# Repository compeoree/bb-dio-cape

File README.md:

bb-dio-cape
===========

Beaglebone Digital I/O Opto Cape

This project contains the Eagle CAD (Version 6.5) files for a four layer circuit board. It maps 15 pins to digital inputs and 16 pins to digital outputs, all of which are optically isolated. It provides pads for a linear (7805) or switching (Murata OKI-78SR-5/1.5-W36H-C) 5v regulator to power the Beaglebone.

Known Issues
============

1) This cape was initially targeted to the Beaglebone White. I attempted to make it compatible with the BeagleBone Black, but I used the wrong pinmux for the eMMC pins.  
Solution:
a) Lose a few inputs/outputs when installed on a BeagleBone Black
b) Remap the affected pins

2) The TLP281 is EOL (End of Life), replace with TLP290

3) The TI DAC7678 requires a 5 volt supply in order to reach the full 5 volt output. This board only provides 3.3v, so the chip can be directly connected to the Beaglebone I2C pins. This limits the DAC to around 3 volts maximum output. A buffer, such as TI PCA9306, would need to be added to raise the DAC7678 to 5v.

4) The MAX3079E will only work in full duplex 4-wire mode. The TX/RX enables are hard wired to always on. They will not work in 2 wire mode, in the current layout.

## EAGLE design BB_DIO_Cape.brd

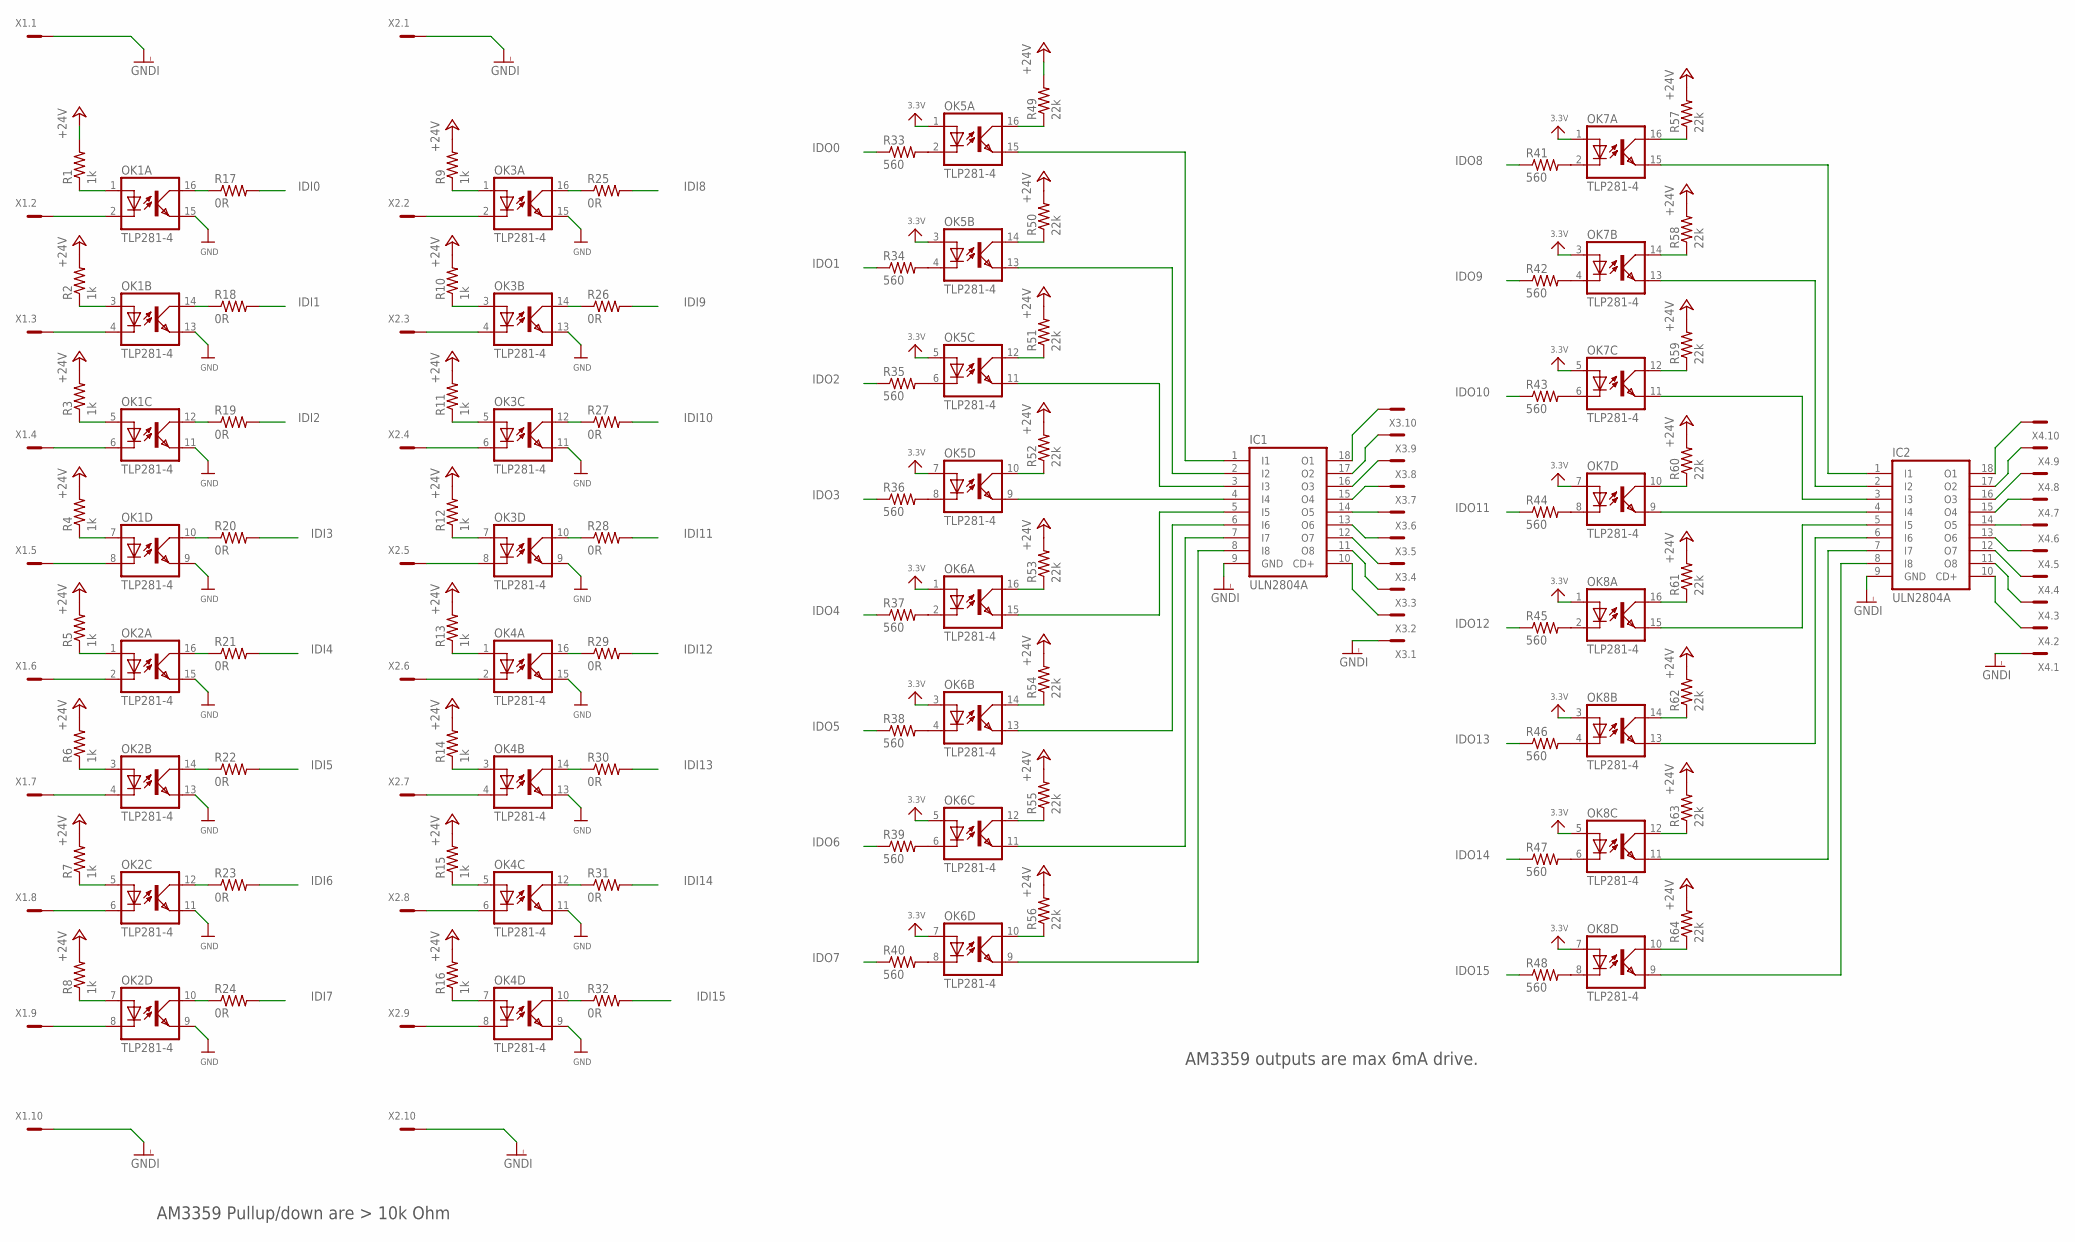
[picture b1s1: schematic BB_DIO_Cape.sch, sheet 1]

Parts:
IC1, IC2: ULN2804A; SO18W
OK1, OK2, OK3, OK4, OK5, OK6, OK7, OK8: TLP281-4; MINI-FLAT-16
R1, R2, R3, R4, R5, R6, R7, R8, R9, R10, R11, R12, R13, R14, R15, R16: 1k; R0603
R17, R18, R19, R20, R21, R22, R23, R24, R25, R26, R27, R28, R29, R30, R31, R32: 0R; R0603
R33, R34, R35, R36, R37, R38, R39, R40, R41, R42, R43, R44, R45, R46, R47, R48: 560; R0603
R49, R50, R51, R52, R53, R54, R55, R56, R57, R58, R59, R60, R61, R62, R63, R64: 22k; R0603
X1, X2, X3, X4: MC10

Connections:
3.3V: OK5.1 (A), OK5.3 (A), OK5.5 (A), OK5.7 (A), OK6.1 (A), OK6.3 (A), OK6.5 (A), OK6.7 (A), OK7.1 (A), OK7.3 (A), OK7.5 (A), OK7.7 (A), OK8.1 (A), OK8.3 (A), OK8.5 (A), OK8.7 (A); also elsewhere on the board
+24V: R1.2, R2.2, R3.2, R4.2, R5.2, R6.2, R7.2, R8.2, R9.2, R10.2, R11.2, R12.2, R13.2, R14.2, R15.2, R16.2, R49.2, R50.2, R51.2, R52.2, R53.2, R54.2, R55.2, R56.2, R57.2, R58.2, R59.2, R60.2, R61.2, R62.2, R63.2, R64.2; also elsewhere on the board
GND: OK1.9 (EMIT), OK1.11 (EMIT), OK1.13 (EMIT), OK1.15 (EMIT), OK2.9 (EMIT), OK2.11 (EMIT), OK2.13 (EMIT), OK2.15 (EMIT), OK3.9 (EMIT), OK3.11 (EMIT), OK3.13 (EMIT), OK3.15 (EMIT), OK4.9 (EMIT), OK4.11 (EMIT), OK4.13 (EMIT), OK4.15 (EMIT); also elsewhere on the board
GNDI: IC1.9 (GND), IC2.9 (GND), X1.1, X1.10, X2.1, X2.10, X3.1, X4.1; also elsewhere on the board
IDI0: R17.2; also elsewhere on the board
IDI1: R18.2; also elsewhere on the board
IDI2: R19.2; also elsewhere on the board
IDI3: R20.2; also elsewhere on the board
IDI4: R21.2; also elsewhere on the board
IDI5: R22.2; also elsewhere on the board
IDI6: R23.2; also elsewhere on the board
IDI7: R24.2; also elsewhere on the board
IDI8: R25.2; also elsewhere on the board
IDI9: R26.2; also elsewhere on the board
IDI10: R27.2; also elsewhere on the board
IDI11: R28.2; also elsewhere on the board
IDI12: R29.2; also elsewhere on the board
IDI13: R30.2; also elsewhere on the board
IDI14: R31.2; also elsewhere on the board
IDI15: R32.2
IDO0: R33.1; also elsewhere on the board
IDO1: R34.1; also elsewhere on the board
IDO2: R35.1; also elsewhere on the board
IDO3: R36.1; also elsewhere on the board
IDO4: R37.1; also elsewhere on the board
IDO5: R38.1; also elsewhere on the board
IDO6: R39.1; also elsewhere on the board
IDO7: R40.1; also elsewhere on the board
IDO8: R41.1; also elsewhere on the board
IDO9: R42.1; also elsewhere on the board
IDO10: R43.1; also elsewhere on the board
IDO11: R44.1; also elsewhere on the board
IDO12: R45.1; also elsewhere on the board
IDO13: R46.1; also elsewhere on the board
IDO14: R47.1; also elsewhere on the board
IDO15: R48.1; also elsewhere on the board
unnamed: OK4.8 (C), X2.9
unnamed: OK4.7 (A), R16.1
unnamed: OK4.5 (A), R15.1
unnamed: OK4.6 (C), X2.8
unnamed: OK4.4 (C), X2.7
unnamed: OK4.3 (A), R14.1
unnamed: OK4.2 (C), X2.6
unnamed: OK4.1 (A), R13.1
unnamed: OK3.8 (C), X2.5
unnamed: OK3.7 (A), R12.1
unnamed: OK3.6 (C), X2.4
unnamed: OK3.5 (A), R11.1
unnamed: OK3.4 (C), X2.3
unnamed: OK3.3 (A), R10.1
unnamed: OK4.10 (COL), R32.1
unnamed: OK4.12 (COL), R31.1
unnamed: OK4.14 (COL), R30.1
unnamed: OK4.16 (COL), R29.1
unnamed: OK3.10 (COL), R28.1
unnamed: OK3.12 (COL), R27.1
unnamed: OK3.14 (COL), R26.1
unnamed: OK2.10 (COL), R24.1
unnamed: OK2.12 (COL), R23.1
unnamed: OK2.14 (COL), R22.1
unnamed: OK2.16 (COL), R21.1
unnamed: OK1.10 (COL), R20.1
unnamed: OK1.12 (COL), R19.1
unnamed: OK1.14 (COL), R18.1
unnamed: OK1.4 (C), X1.3
unnamed: OK1.3 (A), R2.1
unnamed: OK1.5 (A), R3.1
unnamed: OK1.6 (C), X1.4
unnamed: OK1.7 (A), R4.1
unnamed: OK1.8 (C), X1.5
unnamed: OK2.2 (C), X1.6
unnamed: OK2.1 (A), R5.1
unnamed: OK2.3 (A), R6.1
unnamed: OK2.4 (C), X1.7
unnamed: OK2.5 (A), R7.1
unnamed: OK2.6 (C), X1.8
unnamed: OK2.7 (A), R8.1
unnamed: OK2.8 (C), X1.9
unnamed: OK1.2 (C), X1.2
unnamed: OK1.1 (A), R1.1
unnamed: OK1.16 (COL), R17.1
unnamed: OK3.2 (C), X2.2
unnamed: OK3.1 (A), R9.1
unnamed: OK3.16 (COL), R25.1
unnamed: OK5.2 (C), R33.2
unnamed: OK5.4 (C), R34.2
unnamed: OK5.6 (C), R35.2
unnamed: OK5.8 (C), R36.2
unnamed: OK6.2 (C), R37.2
unnamed: OK6.4 (C), R38.2
unnamed: OK6.6 (C), R39.2
unnamed: OK6.8 (C), R40.2
unnamed: OK7.2 (C), R41.2
unnamed: OK7.4 (C), R42.2
unnamed: OK7.6 (C), R43.2
unnamed: OK7.8 (C), R44.2
unnamed: OK8.2 (C), R45.2
unnamed: OK8.4 (C), R46.2
unnamed: OK8.6 (C), R47.2
unnamed: OK8.8 (C), R48.2
unnamed: OK5.16 (COL), R49.1
unnamed: OK5.14 (COL), R50.1
unnamed: OK5.12 (COL), R51.1
unnamed: OK5.10 (COL), R52.1
unnamed: OK6.16 (COL), R53.1
unnamed: OK6.14 (COL), R54.1
unnamed: OK6.12 (COL), R55.1
unnamed: OK6.10 (COL), R56.1
unnamed: IC1.8 (I8), OK6.9 (EMIT)
unnamed: IC1.7 (I7), OK6.11 (EMIT)
unnamed: IC1.6 (I6), OK6.13 (EMIT)
unnamed: IC1.5 (I5), OK6.15 (EMIT)
unnamed: IC1.4 (I4), OK5.9 (EMIT)
unnamed: IC1.3 (I3), OK5.11 (EMIT)
unnamed: IC1.2 (I2), OK5.13 (EMIT)
unnamed: IC1.1 (I1), OK5.15 (EMIT)
unnamed: OK8.14 (COL), R62.1
unnamed: OK8.12 (COL), R63.1
unnamed: OK8.10 (COL), R64.1
unnamed: IC2.8 (I8), OK8.9 (EMIT)
unnamed: IC2.7 (I7), OK8.11 (EMIT)
unnamed: IC2.6 (I6), OK8.13 (EMIT)
unnamed: IC2.5 (I5), OK8.15 (EMIT)
unnamed: OK8.16 (COL), R61.1
unnamed: OK7.10 (COL), R60.1
unnamed: OK7.12 (COL), R59.1
unnamed: IC2.4 (I4), OK7.9 (EMIT)
unnamed: IC2.3 (I3), OK7.11 (EMIT)
unnamed: IC2.2 (I2), OK7.13 (EMIT)
unnamed: OK7.14 (COL), R58.1
unnamed: OK7.16 (COL), R57.1
unnamed: IC2.1 (I1), OK7.15 (EMIT)
unnamed: IC2.18 (O1), X4.10
unnamed: IC2.10 (CD+), X4.2
unnamed: IC2.11 (O8), X4.3
unnamed: IC2.17 (O2), X4.9
unnamed: IC2.12 (O7), X4.4
unnamed: IC2.13 (O6), X4.5
unnamed: IC2.14 (O5), X4.6
unnamed: IC2.15 (O4), X4.7
unnamed: IC2.16 (O3), X4.8
unnamed: IC1.14 (O5), X3.6
unnamed: IC1.13 (O6), X3.5
unnamed: IC1.12 (O7), X3.4
unnamed: IC1.15 (O4), X3.7
unnamed: IC1.16 (O3), X3.8
unnamed: IC1.17 (O2), X3.9
unnamed: IC1.11 (O8), X3.3
unnamed: IC1.10 (CD+), X3.2
unnamed: IC1.18 (O1), X3.10

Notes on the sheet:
AM3359 Pullup/down are > 10k Ohm
AM3359 outputs are max 6mA drive.

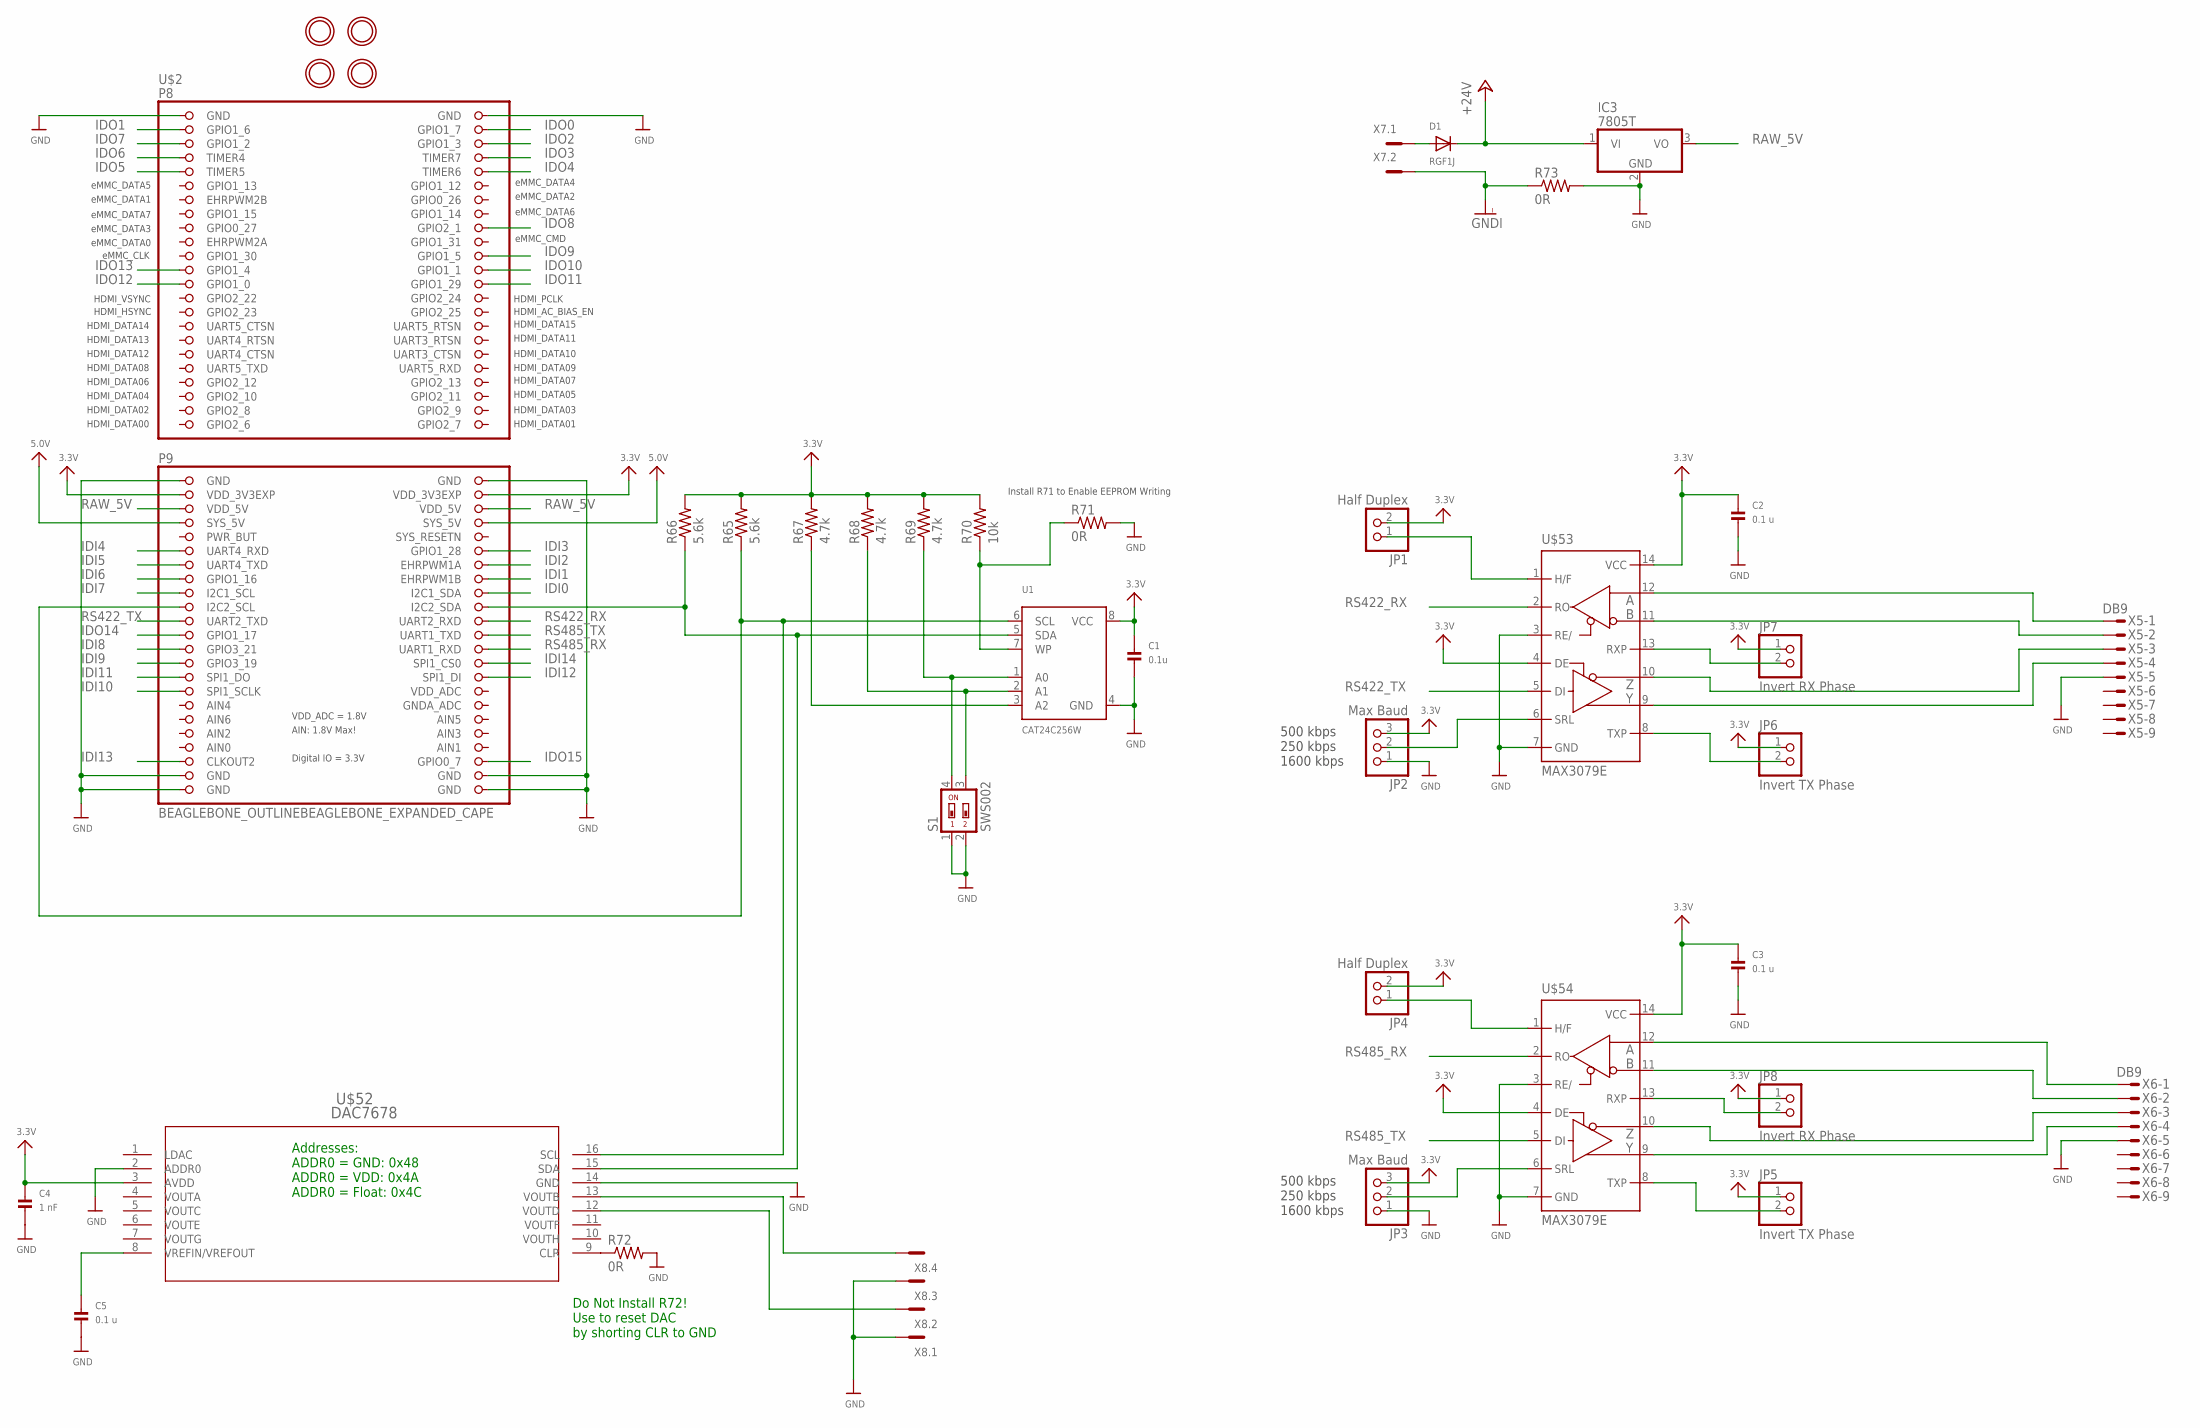
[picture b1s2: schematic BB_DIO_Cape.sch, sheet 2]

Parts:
C1: 0.1u; _0603
C2, C3, C5: 0.1 u; 0603
C4: 1 nF; 0603
D1: RGF1J; SMADIODE
IC3: 7805T; TO220H
JP1, JP4: Half Duplex; 1X02_ROUND
JP2, JP3: Max Baud; 1X03_ROUND
JP5, JP6: Invert TX Phase; 1X02_ROUND
JP7, JP8: Invert RX Phase; 1X02_ROUND
R65, R66: 5.6k; R0603
R67, R68, R69: 4.7k; R0603
R70: 10k; R0603
R71, R72: 0R; R0603
R73: 0R; M1206
S1: SWS002; SMS-002
U1: CAT24C256W; SOIC8_150MIL
U$2: BEAGLEBONE_OUTLINEBEAGLEBONE_EXPANDED_CAPE; BEAGLEBONE_SHIELD
U$22, U$23, U$71, U$72: MOUNTINGHOLE3.0THIN; MOUNTINGHOLE_3.0_PLATEDTHIN
U$52: DAC7678; PW16
U$53, U$54: MAX3079E; SO14
X5, X6: DB9; 182-009-MALE
X7: MC2
X8: MC4

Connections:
3.3V: C1.1, C2.1, C3.1, C4.1, JP1.2, JP2.3, JP3.3, JP4.2, JP5.1, JP6.1, JP7.1, JP8.1, R65.2, R66.2, R67.2, R68.2, R69.2, R70.2, U1.8 (VCC), U$2.49 (VDD_3V3EXP), U$2.50 (VDD_3V3EXP), U$52.3 (AVDD), U$53.4 (DE), U$53.14 (VCC), U$54.4 (DE), U$54.14 (VCC); also elsewhere on the board
5.0V: U$2.53 (SYS_5V), U$2.54 (SYS_5V)
+24V: D1.C, IC3.1 (VI); also elsewhere on the board
GND: C1.2, C2.2, C3.2, C4.2, C5.2, IC3.2 (GND), JP2.1, JP3.1, R71.2, R72.2, R73.2, S1.1, S1.2, U1.4 (GND), U$2.1 (GND), U$2.2 (GND), U$2.47 (GND), U$2.48 (GND), U$2.89 (GND), U$2.90 (GND), U$2.91 (GND), U$2.92 (GND), U$52.2 (ADDR0), U$52.14 (GND), U$53.3 (RE/), U$53.7 (GND), U$54.3 (RE/), U$54.7 (GND), X5.5, X6.5, X8.1, X8.3; also elsewhere on the board
GNDA_ADC: U$2.80 (GNDA_ADC)
GNDI: R73.1, X7.2; also elsewhere on the board
IDI0: U$2.64 (I2C1_SDA); also elsewhere on the board
IDI1: U$2.62 (EHRPWM1B); also elsewhere on the board
IDI2: U$2.60 (EHRPWM1A); also elsewhere on the board
IDI3: U$2.58 (GPIO1_28); also elsewhere on the board
IDI4: U$2.57 (UART4_RXD); also elsewhere on the board
IDI5: U$2.59 (UART4_TXD); also elsewhere on the board
IDI6: U$2.61 (GPIO1_16); also elsewhere on the board
IDI7: U$2.63 (I2C1_SCL); also elsewhere on the board
IDI8: U$2.71 (GPIO3_21); also elsewhere on the board
IDI9: U$2.73 (GPIO3_19); also elsewhere on the board
IDI10: U$2.77 (SPI1_SCLK); also elsewhere on the board
IDI11: U$2.75 (SPI1_DO); also elsewhere on the board
IDI12: U$2.76 (SPI1_DI); also elsewhere on the board
IDI13: U$2.87 (CLKOUT2); also elsewhere on the board
IDI14: U$2.74 (SPI1_CS0); also elsewhere on the board
IDO0: U$2.4 (GPIO1_7); also elsewhere on the board
IDO1: U$2.3 (GPIO1_6); also elsewhere on the board
IDO2: U$2.6 (GPIO1_3); also elsewhere on the board
IDO3: U$2.8 (TIMER7); also elsewhere on the board
IDO4: U$2.10 (TIMER6); also elsewhere on the board
IDO5: U$2.9 (TIMER5); also elsewhere on the board
IDO6: U$2.7 (TIMER4); also elsewhere on the board
IDO7: U$2.5 (GPIO1_2); also elsewhere on the board
IDO8: U$2.18 (GPIO2_1); also elsewhere on the board
IDO9: U$2.22 (GPIO1_5); also elsewhere on the board
IDO10: U$2.24 (GPIO1_1); also elsewhere on the board
IDO11: U$2.26 (GPIO1_29); also elsewhere on the board
IDO12: U$2.25 (GPIO1_0); also elsewhere on the board
IDO13: U$2.23 (GPIO1_4); also elsewhere on the board
IDO14: U$2.69 (GPIO1_17); also elsewhere on the board
IDO15: U$2.88 (GPIO0_7); also elsewhere on the board
unnamed: D1.A, X7.1
unnamed: C5.1, U$52.8 (VREFIN/VREFOUT)
unnamed: R72.1, U$52.9 (CLR)
unnamed: JP3.2, U$54.6 (SRL)
unnamed: R69.1, S1.4, U1.1 (A0)
unnamed: R70.1, R71.1, U1.7 (WP)
unnamed: JP2.2, U$53.6 (SRL)
unnamed: JP7.2, U$53.13 (RXP)
unnamed: JP6.2, U$53.8 (TXP)
unnamed: JP5.2, U$54.8 (TXP)
unnamed: JP4.1, U$54.1 (H/F)
unnamed: JP1.1, U$53.1 (H/F)
unnamed: JP8.2, U$54.13 (RXP)
unnamed: U$52.13 (VOUTB), X8.4
unnamed: U$52.12 (VOUTD), X8.2
unnamed: U$54.9 (Y), X6.4
unnamed: U$53.10 (Z), X5.3
unnamed: U$53.9 (Y), X5.4
unnamed: U$53.12 (A), X5.1
unnamed: U$53.11 (B), X5.2
unnamed: U$54.11 (B), X6.2
unnamed: U$54.12 (A), X6.1
unnamed: U$54.10 (Z), X6.3
unnamed: R68.1, S1.3, U1.2 (A1)
unnamed: R67.1, U1.3 (A2)
RAW_5V: IC3.3 (VO), U$2.51 (VDD_5V), U$2.52 (VDD_5V)
RS422_RX: U$2.68 (UART2_RXD), U$53.2 (RO)
RS422_TX: U$2.67 (UART2_TXD), U$53.5 (DI)
RS485_RX: U$2.72 (UART1_RXD), U$54.2 (RO)
RS485_TX: U$2.70 (UART1_TXD), U$54.5 (DI)
SCL: R65.1, U1.6 (SCL), U$2.65 (I2C2_SCL), U$52.16 (SCL)
SDA: R66.1, U1.5 (SDA), U$2.66 (I2C2_SDA), U$52.15 (SDA)
VDD_ADC: U$2.78 (VDD_ADC)

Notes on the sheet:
HDMI_VSYNC
HDMI_PCLK
HDMI_HSYNC
HDMI_AC_BIAS_EN
HDMI_DATA14
HDMI_DATA15
HDMI_DATA13
HDMI_DATA11
HDMI_DATA12
HDMI_DATA10
HDMI_DATA08
HDMI_DATA09
HDMI_DATA06
HDMI_DATA07
HDMI_DATA04
HDMI_DATA05
HDMI_DATA02
HDMI_DATA03
HDMI_DATA00
HDMI_DATA01
eMMC_DATA5
eMMC_DATA4
eMMC_DATA1
eMMC_DATA2
eMMC_DATA7
eMMC_DATA6
eMMC_DATA3
eMMC_DATA0
eMMC_CMD
eMMC_CLK
Install R71 to Enable EEPROM Writing
Addresses: ADDR0 = GND: 0x48 ADDR0 = VDD: 0x4A ADDR0 = Float: 0x4C
Do Not Install R72! Use to reset DAC by shorting CLR to GND
500 kbps 250 kbps 1600 kbps

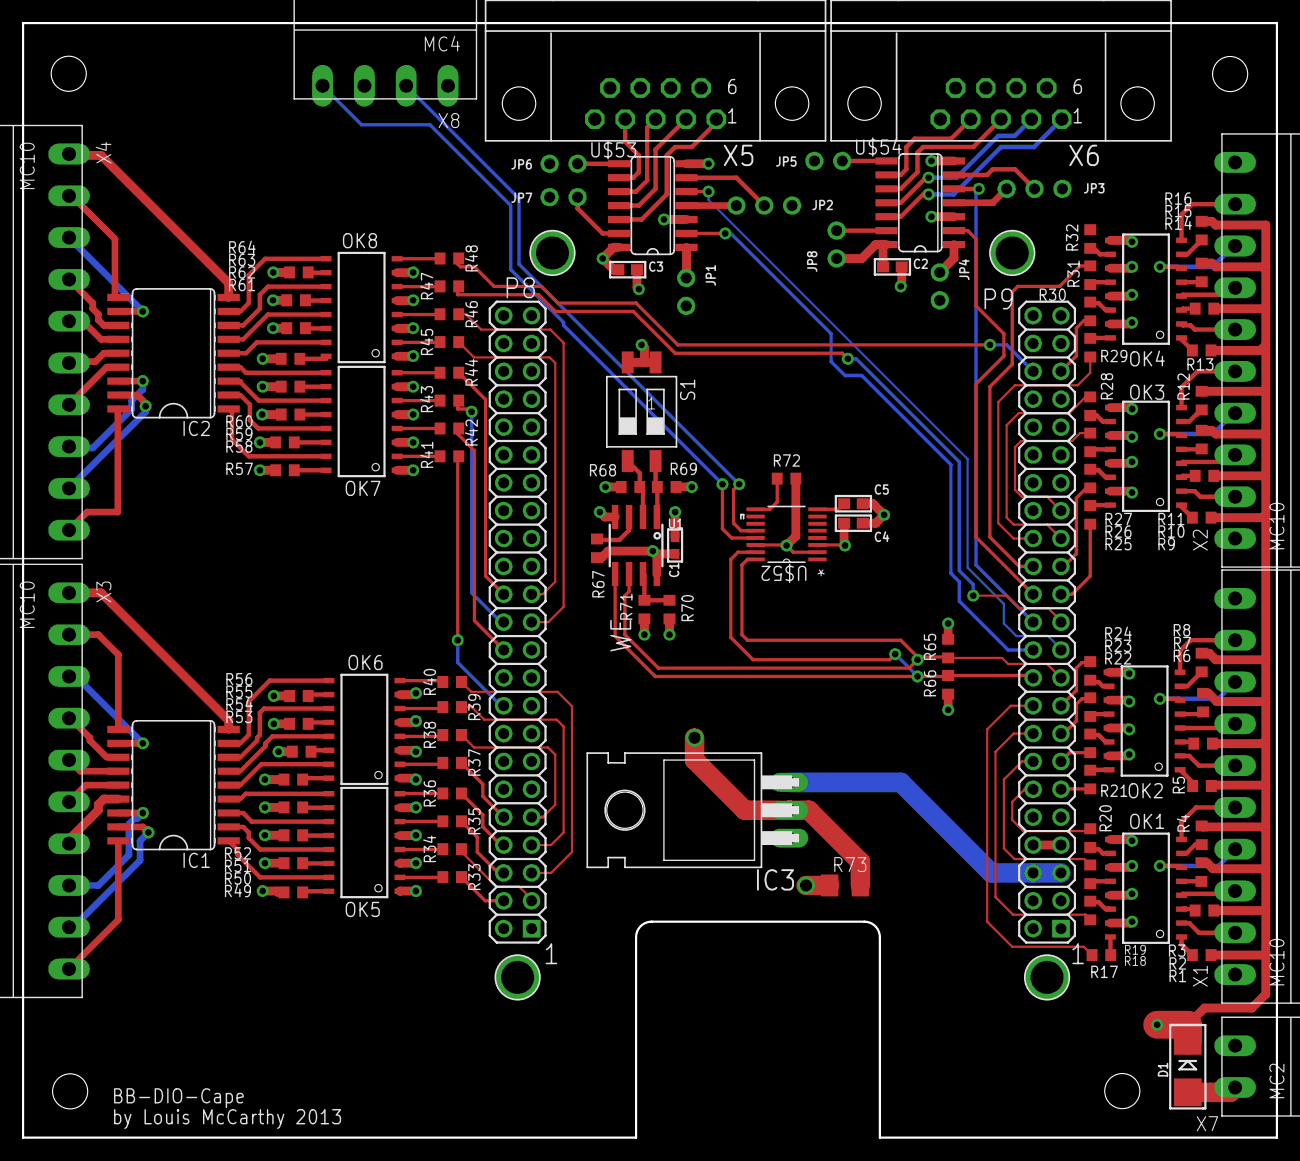
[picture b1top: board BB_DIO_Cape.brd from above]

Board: 4 copper layers, 114.3 x 101.6 mm, 116 parts (0 on the bottom side), 182 nets.

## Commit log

2014-03-04 Changed to CC Attribution 4.0 License
2014-03-04 Added project specifics to README
2014-03-04 Added project files
2014-03-17 Added device tree overlay source file
